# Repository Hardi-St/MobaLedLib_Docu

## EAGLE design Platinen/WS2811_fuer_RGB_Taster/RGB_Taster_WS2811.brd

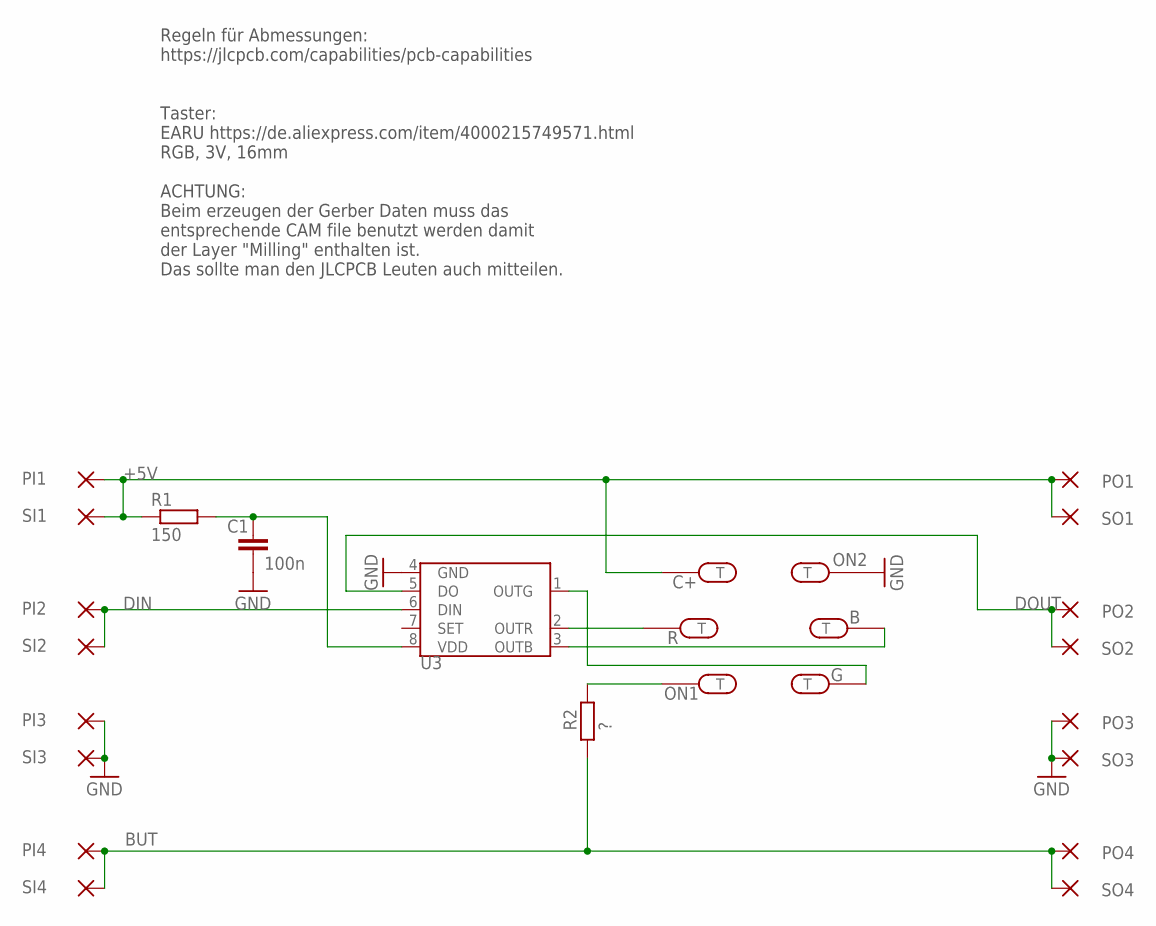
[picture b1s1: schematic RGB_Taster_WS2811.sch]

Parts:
B: LANG_LOCH2
C1: 100n; C0603
C+: LANG_LOCH2
G: LANG_LOCH2
ON1, ON2: LANG_LOCH2
PI1, PI2, PI3, PI4: SMD2; SMD1,27-2,54
PO1, PO2, PO3, PO4: SMD2; SMD1,27-2,54
R: LANG_LOCH2
R1: 150; RCL_R0603
R2: ?; RCL_R0603
SI1, SI2, SI3, SI4: SMD2; SMD1,27-2,54
SO1, SO2, SO3, SO4: SMD2; SMD1,27-2,54
U3: WS2811; SOP8

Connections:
+5V: C+.P$1, C+.P$2, PI1.1, PO1.1, R1.1, SI1.1, SO1.1
BUT: PI4.1, PO4.1, R2.1, SI4.1, SO4.1
DIN: PI2.1, SI2.1, U3.6 (DIN)
DOUT: PO2.1, SO2.1, U3.5 (DO)
GND: C1.2, ON2.P$1, ON2.P$2, PI3.1, PO3.1, SI3.1, SO3.1, U3.4 (GND)
unnamed: B.P$1, B.P$2, U3.3 (OUTB)
unnamed: R.P$1, R.P$2, U3.2 (OUTR)
unnamed: C1.1, R1.2, U3.8 (VDD)
unnamed: G.P$1, G.P$2, U3.1 (OUTG)
unnamed: ON1.P$1, ON1.P$2, R2.2

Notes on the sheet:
Regeln für Abmessungen: https://jlcpcb.com/capabilities/pcb-capabilities Taster: EARU https://de.aliexpress.com/item/4000215749571.html RGB, 3V, 16mm ACHTUNG: Beim erzeugen der Gerber Daten muss das entsprechende CAM file benutzt werden damit der Layer "Milling" enthalten ist. Das sollte man den JL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

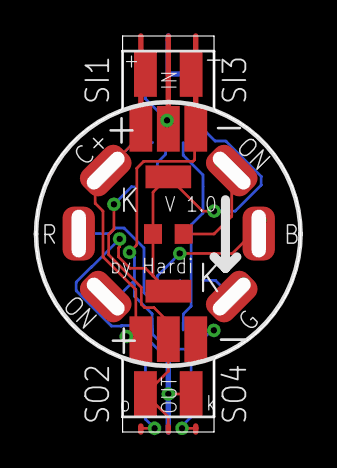
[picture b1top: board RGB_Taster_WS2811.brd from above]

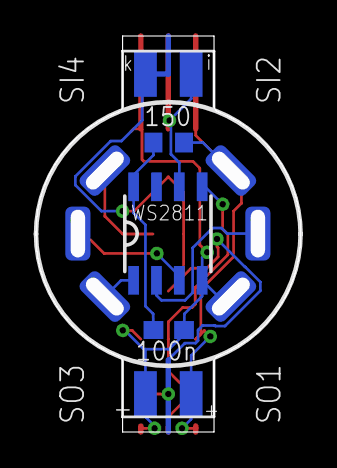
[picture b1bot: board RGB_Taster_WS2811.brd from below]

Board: 2 copper layers, 14.7 x 22.0 mm, 26 parts (7 on the bottom side), 10 nets.

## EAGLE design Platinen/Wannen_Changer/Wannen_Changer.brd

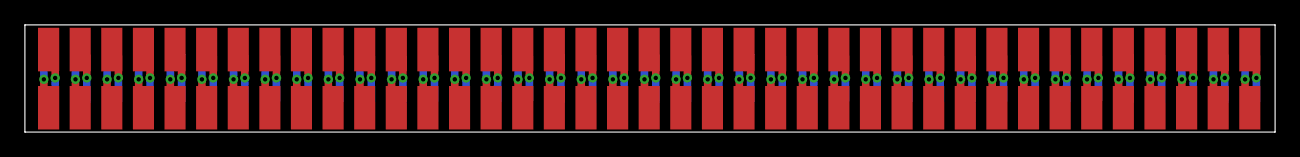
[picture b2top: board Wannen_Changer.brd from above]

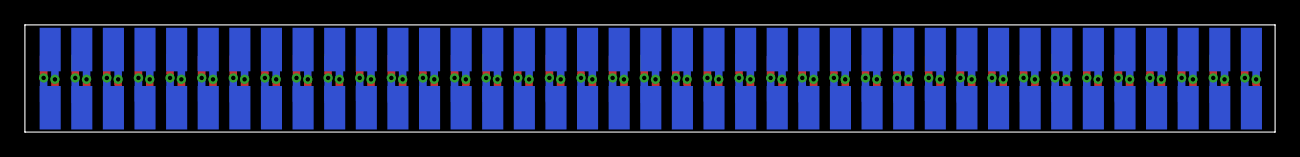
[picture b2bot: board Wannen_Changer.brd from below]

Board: 2 copper layers, 100.5 x 8.6 mm, 78 parts (39 on the bottom side), 78 nets.

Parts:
X1, X2, X3, X4, X5, X6, X7, X8, X9, X10, X11, X12, X13, X14, X15, X16, X17, X18, X19, X20, X21, X22, X23, X24, X25, X26, X27, X28, X29, X30, X31, X32, X33, X34, X35, X36, X37, X38, X39, X40, X41, X42, X43, X44, X45, X46, X47, X48, X49, X50, X51, X52, X53, X54, X55, X56, X57, X58, X59, X60, X61, X62, X63, X64, X65, X66, X67, X68, X69, X70, X71, X72, X73, X74, X75, X76, X77, X78: WANNE_D

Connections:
unnamed: X1.1, X2.1
unnamed: X1.2, X2.2
unnamed: X3.1, X4.1
unnamed: X3.2, X4.2
unnamed: X5.1, X6.1
unnamed: X5.2, X6.2
unnamed: X7.1, X8.1
unnamed: X7.2, X8.2
unnamed: X9.1, X10.1
unnamed: X9.2, X10.2
unnamed: X11.1, X12.1
unnamed: X11.2, X12.2
unnamed: X13.1, X14.1
unnamed: X13.2, X14.2
unnamed: X15.1, X16.1
unnamed: X15.2, X16.2
unnamed: X17.1, X18.1
unnamed: X17.2, X18.2
unnamed: X19.1, X20.1
unnamed: X19.2, X20.2
unnamed: X21.1, X22.1
unnamed: X21.2, X22.2
unnamed: X23.1, X24.1
unnamed: X23.2, X24.2
unnamed: X25.1, X26.1
unnamed: X25.2, X26.2
unnamed: X27.1, X28.1
unnamed: X27.2, X28.2
unnamed: X29.1, X30.1
unnamed: X29.2, X30.2
unnamed: X31.1, X32.1
unnamed: X31.2, X32.2
unnamed: X33.1, X34.1
unnamed: X33.2, X34.2
unnamed: X35.1, X36.1
unnamed: X35.2, X36.2
unnamed: X37.1, X38.1
unnamed: X37.2, X38.2
unnamed: X39.1, X40.1
unnamed: X39.2, X40.2
unnamed: X41.1, X42.1
unnamed: X41.2, X42.2
unnamed: X43.1, X44.1
unnamed: X43.2, X44.2
unnamed: X45.1, X46.1
unnamed: X45.2, X46.2
unnamed: X47.1, X48.1
unnamed: X47.2, X48.2
unnamed: X49.1, X50.1
unnamed: X49.2, X50.2
unnamed: X51.1, X52.1
unnamed: X51.2, X52.2
unnamed: X53.1, X54.1
unnamed: X53.2, X54.2
unnamed: X55.1, X56.1
unnamed: X55.2, X56.2
unnamed: X57.1, X58.1
unnamed: X57.2, X58.2
unnamed: X59.1, X60.1
unnamed: X59.2, X60.2
unnamed: X61.1, X62.1
unnamed: X61.2, X62.2
unnamed: X63.1, X64.1
unnamed: X63.2, X64.2
unnamed: X65.1, X66.1
unnamed: X65.2, X66.2
unnamed: X67.1, X68.1
unnamed: X67.2, X68.2
unnamed: X69.1, X70.1
unnamed: X69.2, X70.2
unnamed: X71.1, X72.1
unnamed: X71.2, X72.2
unnamed: X73.1, X74.1
unnamed: X73.2, X74.2
unnamed: X75.1, X76.1
unnamed: X75.2, X76.2
unnamed: X77.1, X78.1
unnamed: X77.2, X78.2
